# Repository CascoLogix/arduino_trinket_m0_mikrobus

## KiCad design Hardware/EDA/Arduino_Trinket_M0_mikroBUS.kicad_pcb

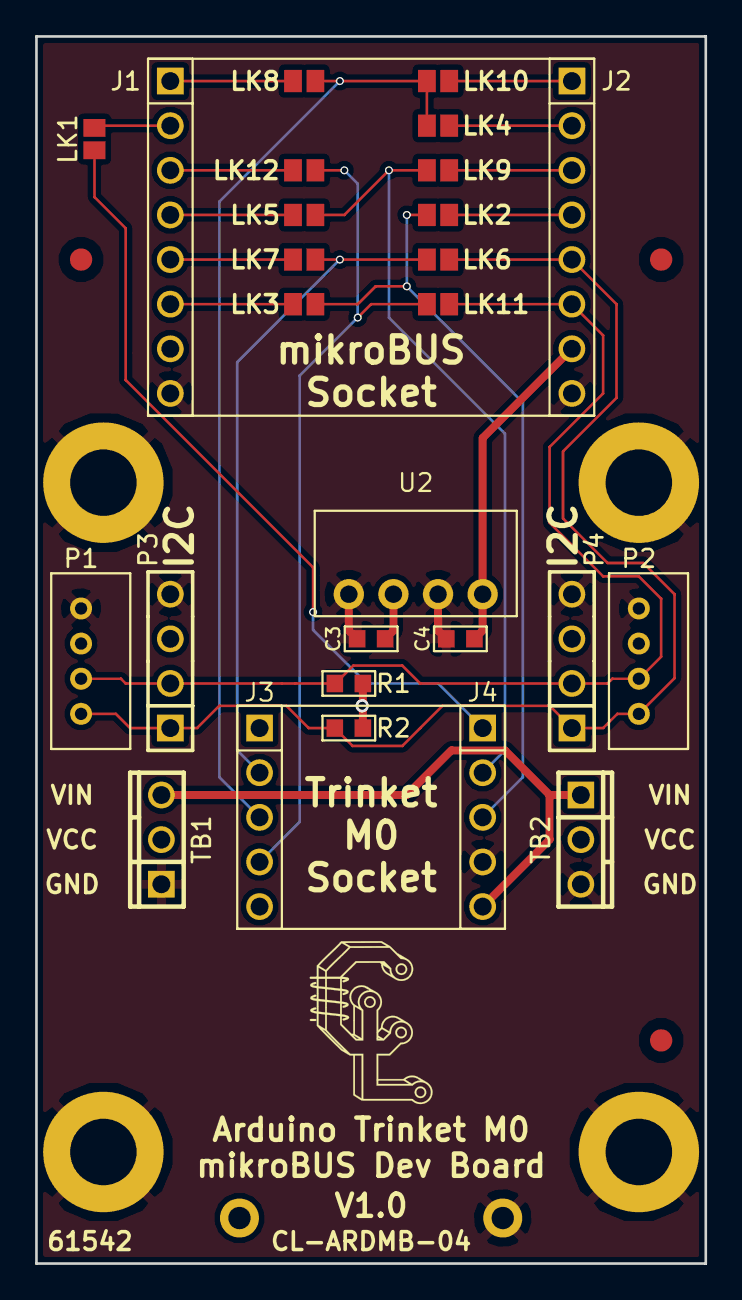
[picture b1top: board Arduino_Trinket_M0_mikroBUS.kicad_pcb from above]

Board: 2 copper layers, 38.1 x 69.8 mm, 36 parts (1 on the bottom side), 22 nets.

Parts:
B2: 2xAA; Keystone_2462_2AA
C3, C4: 1uF; 0603
G1: Casco_Logix_Logo; Casco_Logix_Logo_7x7MM
J1, J2: HEADER_F_2.54MM_1R8P_ST_AU_PTH
J3, J4: HEADER_F_2.54MM_1R5P_ST_AU_PTH
LK1: N.O.; SOLDER_LINK_NO
LK2: TXD; SOLDER_LINK_NO
LK3: MOSI; SOLDER_LINK_NO
LK4: RXD; SOLDER_LINK_NO
LK5: SCK; SOLDER_LINK_NO
LK6, LK11: SCL; SOLDER_LINK_NO
LK7, LK12: MISO; SOLDER_LINK_NO
LK8: AN; SOLDER_LINK_NO
LK9: INT; SOLDER_LINK_NO
LK10: PWM; SOLDER_LINK_NO
M1, M2, M3: FID; FIDUCIAL
MH1, MH2, MH3, MH4: MTG_HOLE; MH_#6
P1, P2: HEADER_M_2.54MM_1R4P_ST_AU_PTH; PH_2.0_PTH
P3, P4: HEADER_M_2.54MM_1R4P_ST_AU_PTH
R1, R2: 4.7k; R0603
TB1, TB2: OSTVN_1x3; TB_100MIL_1R3P_PTH
U2: Recom_DC_DC_Conv; Recom_ROE-3.305S

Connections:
3V3: B2.1, C3.1, J1.7, J3.1, P1.3, P2.3, P3.3, P4.3, R1.1, R2.1, TB1.2, TB2.2, U2.2
5.0V: C4.1, J2.7, U2.4
AN: J1.1, LK8.1
CS: J1.3, LK12.1
D0: J3.4, LK11.2, LK12.2
D1: J3.3, LK8.2, LK9.2, LK10.2
D2: J3.2, LK6.2, LK7.2
D3: J4.2, LK4.2, LK5.2
D4: J4.3, LK2.2, LK3.2
GND: B2.2, C3.2, C4.2, J1.8, J2.8, J4.4, MH1.~, MH2.~, MH3.~, MH4.~, P1.4, P2.4, P3.4, P4.4, TB1.1, TB2.3, U2.1, U2.3
INT: J2.2, LK9.1
MISO: J1.5, LK7.1
MOSI: J1.6, LK3.1
PWM: J2.1, LK10.1
RST: J4.1, LK1.1
RXD: J2.3, LK4.1
SCK: J1.4, LK5.1
SCL: J2.5, LK6.1, P1.1, P2.1, P3.1, P4.1, R2.2
SDA: J2.6, LK11.1, P1.2, P2.2, P3.2, P4.2, R1.2
TXD: J2.4, LK2.1
VIN: J4.5, TB1.3, TB2.1
mikroBUS_RST: J1.2, LK1.2

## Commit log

2017-12-29 Initial commit.
2017-12-29 Completed layout, generated PCB render image, schematic and gerbers.
2017-12-29 Corrected mistake in silkscreen artwork and regenerated PCB render image and gerbers.
